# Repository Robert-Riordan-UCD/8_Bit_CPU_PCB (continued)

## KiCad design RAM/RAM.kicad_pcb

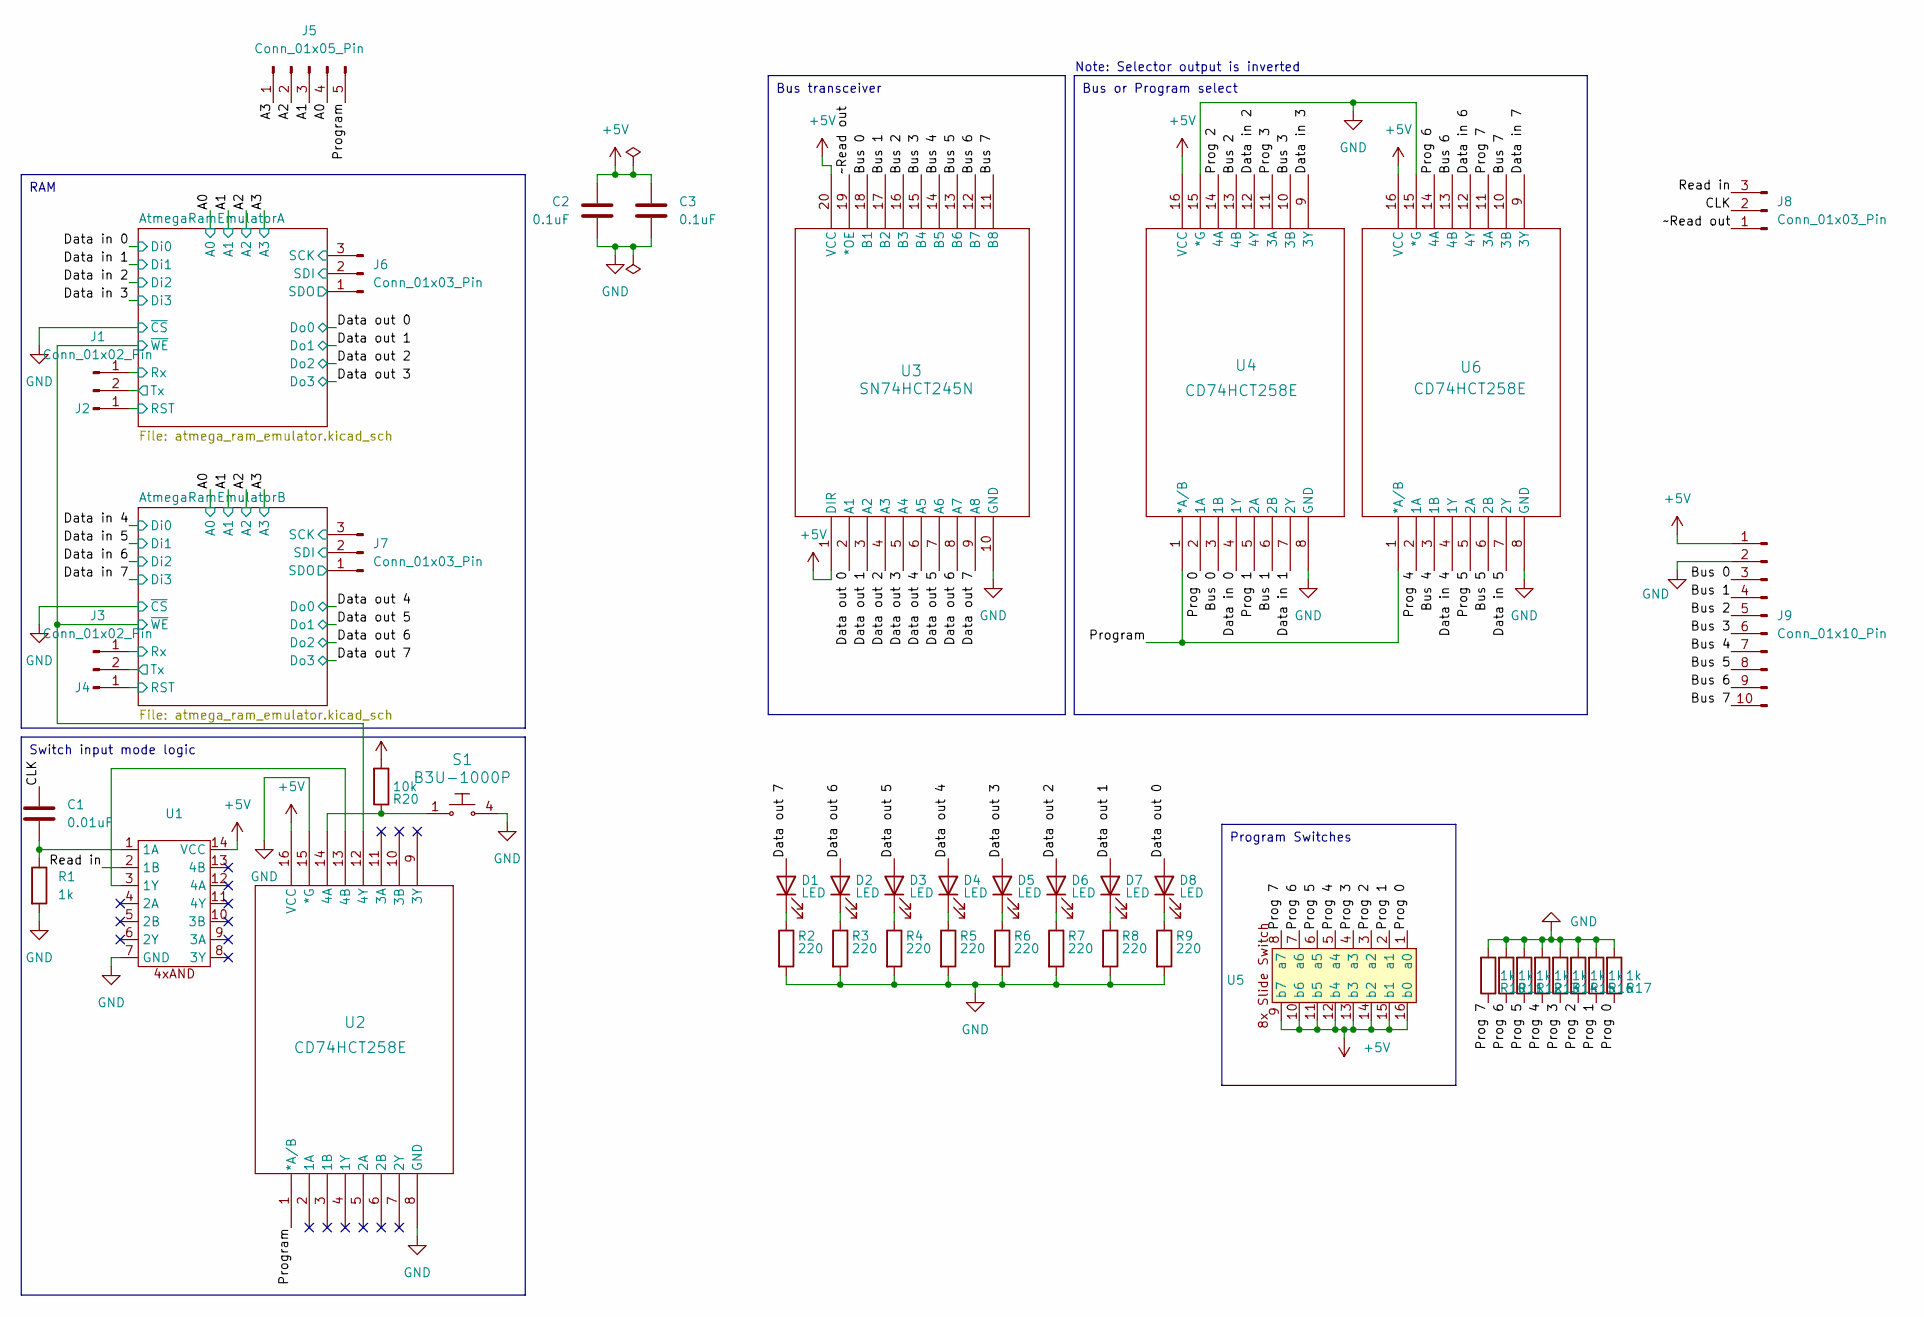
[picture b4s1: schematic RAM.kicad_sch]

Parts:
C1: 0.01uF; C_Disc_D5.0mm_W2.5mm_P2.50mm
C2, C3: 0.1uF; C_Disc_D5.0mm_W2.5mm_P2.50mm
D1, D2, D3, D4, D5, D6, D7, D8: LED; LED_D5.0mm
J1, J3: Conn_01x02_Pin; PinHeader_1x02_P2.54mm_Vertical
J2, J4: Conn_01x01_Pin; PinHeader_1x01_P2.54mm_Vertical
J5: Conn_01x05_Pin; PinHeader_1x05_P2.54mm_Vertical
J6, J7, J8: Conn_01x03_Pin; PinHeader_1x03_P2.54mm_Vertical
J9: Conn_01x10_Pin; PinHeader_1x10_P2.54mm_Vertical
R1, R10, R11, R12, R13, R14, R15, R16, R17: 1k; CF_series_Resistors_THT
R2, R3, R4, R5, R6, R7, R8, R9: 220; CF_series_Resistors_THT
R20: 10k; CF_series_Resistors_THT
S1: B3U-1000P; tactile_switch; MPN B3U-1000P; Digi-Key_PN SW1020CT-ND
U1: 4x_and
U2, U4, U6: CD74HCT258E; 2_to_1_selector
U3: SN74HCT245N; 8x_tristate_transceiver
U5: DIP-16_W7.62mm

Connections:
+5V: C2.1, C3.1, J9.1, R20.2, U1.14 (VCC), U2.16 (VCC), U3.1 (DIR), U3.20 (VCC), U4.16 (VCC), U5.9 (b7), U5.10 (b6), U5.11 (b5), U5.12 (b4), U5.13 (b3), U5.14 (b2), U5.15 (b1), U5.16 (b0), U6.16 (VCC); also elsewhere on the board
/A0: J5.4; also elsewhere on the board
/A1: J5.3; also elsewhere on the board
/A2: J5.2; also elsewhere on the board
/A3: J5.1; also elsewhere on the board
/AtmegaRamEmulatorA/RST: J2.1; also elsewhere on the board
/AtmegaRamEmulatorA/Rx: J1.1; also elsewhere on the board
/AtmegaRamEmulatorA/SCK: J6.3; also elsewhere on the board
/AtmegaRamEmulatorA/SDI: J6.2; also elsewhere on the board
/AtmegaRamEmulatorA/SDO: J6.1; also elsewhere on the board
/AtmegaRamEmulatorA/Tx: J1.2; also elsewhere on the board
/AtmegaRamEmulatorA/~WE: U2.12 (4Y); also elsewhere on the board
/AtmegaRamEmulatorB/RST: J4.1; also elsewhere on the board
/AtmegaRamEmulatorB/Rx: J3.1; also elsewhere on the board
/AtmegaRamEmulatorB/SCK: J7.3; also elsewhere on the board
/AtmegaRamEmulatorB/SDI: J7.2; also elsewhere on the board
/AtmegaRamEmulatorB/SDO: J7.1; also elsewhere on the board
/AtmegaRamEmulatorB/Tx: J3.2; also elsewhere on the board
/Bus 0: J9.3, U3.18 (B1), U4.3 (1B)
/Bus 1: J9.4, U3.17 (B2), U4.6 (2B)
/Bus 2: J9.5, U3.16 (B3), U4.13 (4B)
/Bus 3: J9.6, U3.15 (B4), U4.10 (3B)
/Bus 4: J9.7, U3.14 (B5), U6.3 (1B)
/Bus 5: J9.8, U3.13 (B6), U6.6 (2B)
/Bus 6: J9.9, U3.12 (B7), U6.13 (4B)
/Bus 7: J9.10, U3.11 (B8), U6.10 (3B)
/CLK: C1.1, J8.2
/Data in 0: U4.4 (1Y); also elsewhere on the board
/Data in 1: U4.7 (2Y); also elsewhere on the board
/Data in 2: U4.12 (4Y); also elsewhere on the board
/Data in 3: U4.9 (3Y); also elsewhere on the board
/Data in 4: U6.4 (1Y); also elsewhere on the board
/Data in 5: U6.7 (2Y); also elsewhere on the board
/Data in 6: U6.12 (4Y); also elsewhere on the board
/Data in 7: U6.9 (3Y); also elsewhere on the board
/Data out 0: D8.2 (A), U3.2 (A1); also elsewhere on the board
/Data out 1: D7.2 (A), U3.3 (A2); also elsewhere on the board
/Data out 2: D6.2 (A), U3.4 (A3); also elsewhere on the board
/Data out 3: D5.2 (A), U3.5 (A4); also elsewhere on the board
/Data out 4: D4.2 (A), U3.6 (A5); also elsewhere on the board
/Data out 5: D3.2 (A), U3.7 (A6); also elsewhere on the board
/Data out 6: D2.2 (A), U3.8 (A7); also elsewhere on the board
/Data out 7: D1.2 (A), U3.9 (A8); also elsewhere on the board
/Prog 0: R17.1, U4.2 (1A), U5.1 (a0)
/Prog 1: R16.1, U4.5 (2A), U5.2 (a1)
/Prog 2: R15.1, U4.14 (4A), U5.3 (a2)
/Prog 3: R14.1, U4.11 (3A), U5.4 (a3)
/Prog 4: R13.1, U5.5 (a4), U6.2 (1A)
/Prog 5: R12.1, U5.6 (a5), U6.5 (2A)
/Prog 6: R11.1, U5.7 (a6), U6.14 (4A)
/Prog 7: R10.1, U5.8 (a7), U6.11 (3A)
/Program: J5.5, U2.1 (*A/B), U4.1 (*A/B), U6.1 (*A/B)
/Read in: J8.3, U1.2 (1B)
/~Read out: J8.1, U3.19 (*OE)
GND: C2.2, C3.2, J9.2, R1.2, R2.2, R3.2, R4.2, R5.2, R6.2, R7.2, R8.2, R9.2, R10.2, R11.2, R12.2, R13.2, R14.2, R15.2, R16.2, R17.2, S1.4, U1.7 (GND), U2.8 (GND), U2.15 (*G), U3.10 (GND), U4.8 (GND), U4.15 (*G), U6.8 (GND), U6.15 (*G); also elsewhere on the board
unnamed: D1.1 (K), R2.1
unnamed: D2.1 (K), R3.1
unnamed: D3.1 (K), R4.1
unnamed: D4.1 (K), R5.1
unnamed: D5.1 (K), R6.1
unnamed: D6.1 (K), R7.1
unnamed: D7.1 (K), R8.1
unnamed: D8.1 (K), R9.1
unnamed: C1.2, R1.1, U1.1 (1A)
unnamed: U1.3 (1Y), U2.13 (4B)
unnamed: R20.1, S1.1, U2.14 (4A)

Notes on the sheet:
Program Switches
Switch input mode logic
Bus or Program select
RAM
Bus transceiver
Note: Selector output is inverted

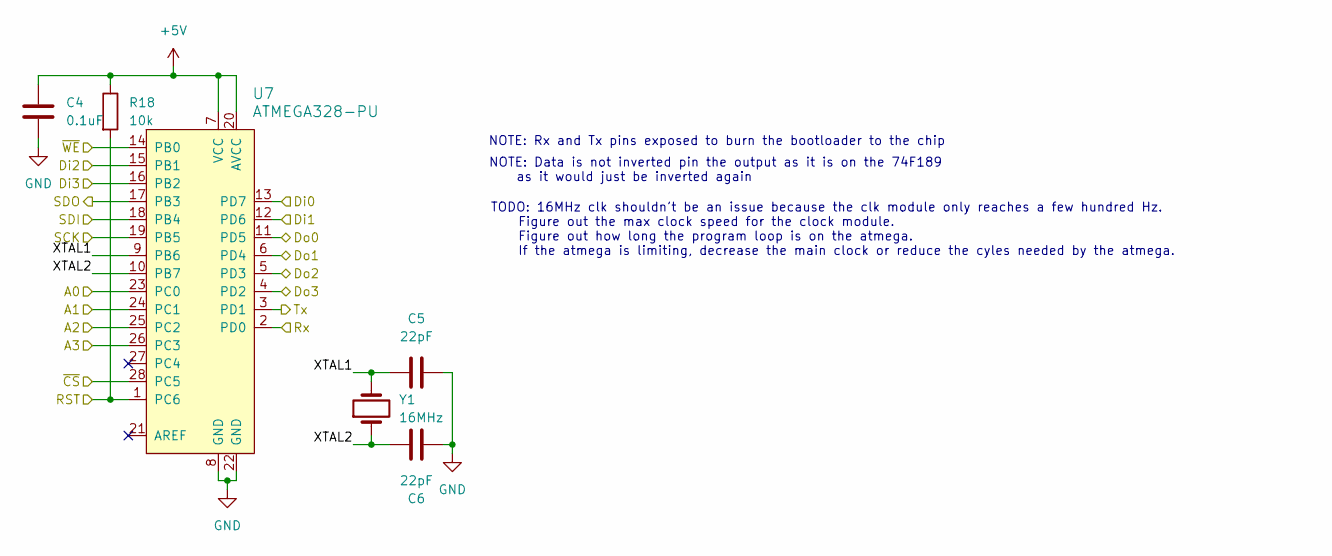
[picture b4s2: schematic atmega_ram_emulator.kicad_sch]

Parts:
C4: 0.1uF; Cp_2mm_pin_spacing
C5, C6: 22pF; C_Disc_D5.0mm_W2.5mm_P2.50mm
R18: 10k; CF_series_Resistors_THT
U7: ATMEGA328-PU; DIP787W46P254L3467H508Q28; MPN ATMEGA328-PU; Digi-Key_PN ATMEGA328-PU-ND
Y1: 16MHz; 16MHzCrystalOscillator

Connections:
+5V: C4.1, R18.1, U7.7 (VCC), U7.20 (AVCC); also elsewhere on the board
/A0: U7.23 (PC0); also elsewhere on the board
/A1: U7.24 (PC1); also elsewhere on the board
/A2: U7.25 (PC2); also elsewhere on the board
/A3: U7.26 (PC3); also elsewhere on the board
/AtmegaRamEmulatorA/RST: R18.2, U7.1 (PC6); also elsewhere on the board
/AtmegaRamEmulatorA/Rx: U7.2 (PD0); also elsewhere on the board
/AtmegaRamEmulatorA/SCK: U7.19 (PB5); also elsewhere on the board
/AtmegaRamEmulatorA/SDI: U7.18 (PB4); also elsewhere on the board
/AtmegaRamEmulatorA/SDO: U7.17 (PB3); also elsewhere on the board
/AtmegaRamEmulatorA/Tx: U7.3 (PD1); also elsewhere on the board
/AtmegaRamEmulatorA/XTAL1: C5.1, U7.9 (PB6), Y1.2
/AtmegaRamEmulatorA/XTAL2: C6.2, U7.10 (PB7), Y1.1
/AtmegaRamEmulatorA/~WE: U7.14 (PB0); also elsewhere on the board
/Data in 0: U7.13 (PD7); also elsewhere on the board
/Data in 1: U7.12 (PD6); also elsewhere on the board
/Data in 2: U7.15 (PB1); also elsewhere on the board
/Data in 3: U7.16 (PB2); also elsewhere on the board
/Data out 0: U7.11 (PD5); also elsewhere on the board
/Data out 1: U7.6 (PD4); also elsewhere on the board
/Data out 2: U7.5 (PD3); also elsewhere on the board
/Data out 3: U7.4 (PD2); also elsewhere on the board
GND: C4.2, C5.2, C6.1, U7.8 (GND), U7.22 (GND), U7.28 (PC5); also elsewhere on the board

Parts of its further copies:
C7: 0.1uF; Cp_2mm_pin_spacing
C8, C9: 22pF; C_Disc_D5.0mm_W2.5mm_P2.50mm
R19: 10k; CF_series_Resistors_THT
U8: ATMEGA328-PU; DIP787W46P254L3467H508Q28; MPN ATMEGA328-PU; Digi-Key_PN ATMEGA328-PU-ND
Y2: 16MHz; 16MHzCrystalOscillator

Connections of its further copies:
+5V: C7.1, R19.1, U8.7 (VCC), U8.20 (AVCC); also elsewhere on the board
/A0: U8.23 (PC0); also elsewhere on the board
/A1: U8.24 (PC1); also elsewhere on the board
/A2: U8.25 (PC2); also elsewhere on the board
/A3: U8.26 (PC3); also elsewhere on the board
/AtmegaRamEmulatorA/~WE: U8.14 (PB0); also elsewhere on the board
/AtmegaRamEmulatorB/RST: R19.2, U8.1 (PC6); also elsewhere on the board
/AtmegaRamEmulatorB/Rx: U8.2 (PD0); also elsewhere on the board
/AtmegaRamEmulatorB/SCK: U8.19 (PB5); also elsewhere on the board
/AtmegaRamEmulatorB/SDI: U8.18 (PB4); also elsewhere on the board
/AtmegaRamEmulatorB/SDO: U8.17 (PB3); also elsewhere on the board
/AtmegaRamEmulatorB/Tx: U8.3 (PD1); also elsewhere on the board
/AtmegaRamEmulatorB/XTAL1: C8.1, U8.9 (PB6), Y2.2
/AtmegaRamEmulatorB/XTAL2: C9.2, U8.10 (PB7), Y2.1
/Data in 4: U8.13 (PD7); also elsewhere on the board
/Data in 5: U8.12 (PD6); also elsewhere on the board
/Data in 6: U8.15 (PB1); also elsewhere on the board
/Data in 7: U8.16 (PB2); also elsewhere on the board
/Data out 4: U8.11 (PD5); also elsewhere on the board
/Data out 5: U8.6 (PD4); also elsewhere on the board
/Data out 6: U8.5 (PD3); also elsewhere on the board
/Data out 7: U8.4 (PD2); also elsewhere on the board
GND: C7.2, C8.2, C9.1, U8.8 (GND), U8.22 (GND), U8.28 (PC5); also elsewhere on the board

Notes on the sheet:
NOTE: Rx and Tx pins exposed to burn the bootloader to the chip
TODO: 16MHz clk shouldn't be an issue because the clk module only reaches a few hundred Hz. Figure out the max clock speed for the clock module. Figure out how long the program loop is on the atmega. If the atmega is limiting, decrease the main clock or reduce the cyles needed by the atmega.
NOTE: Data is not inverted pin the output as it is on the 74F189 as it would just be inverted again

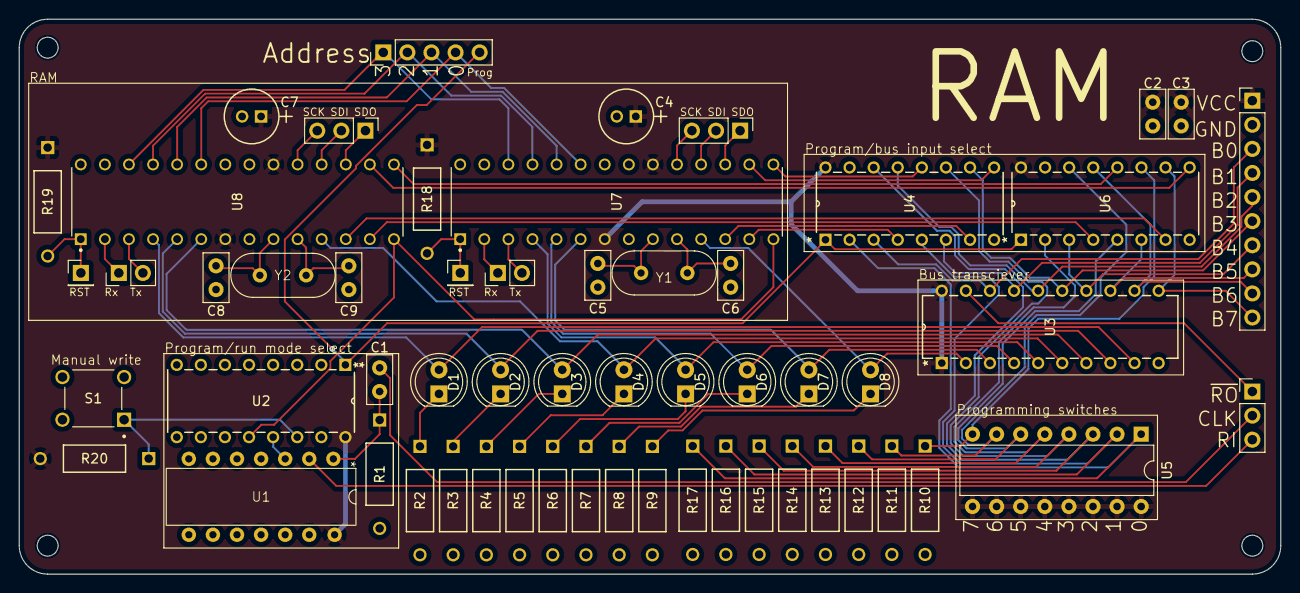
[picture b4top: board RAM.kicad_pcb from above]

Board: 2 copper layers, 133.0 x 58.5 mm, 57 parts (0 on the bottom side), 70 nets.

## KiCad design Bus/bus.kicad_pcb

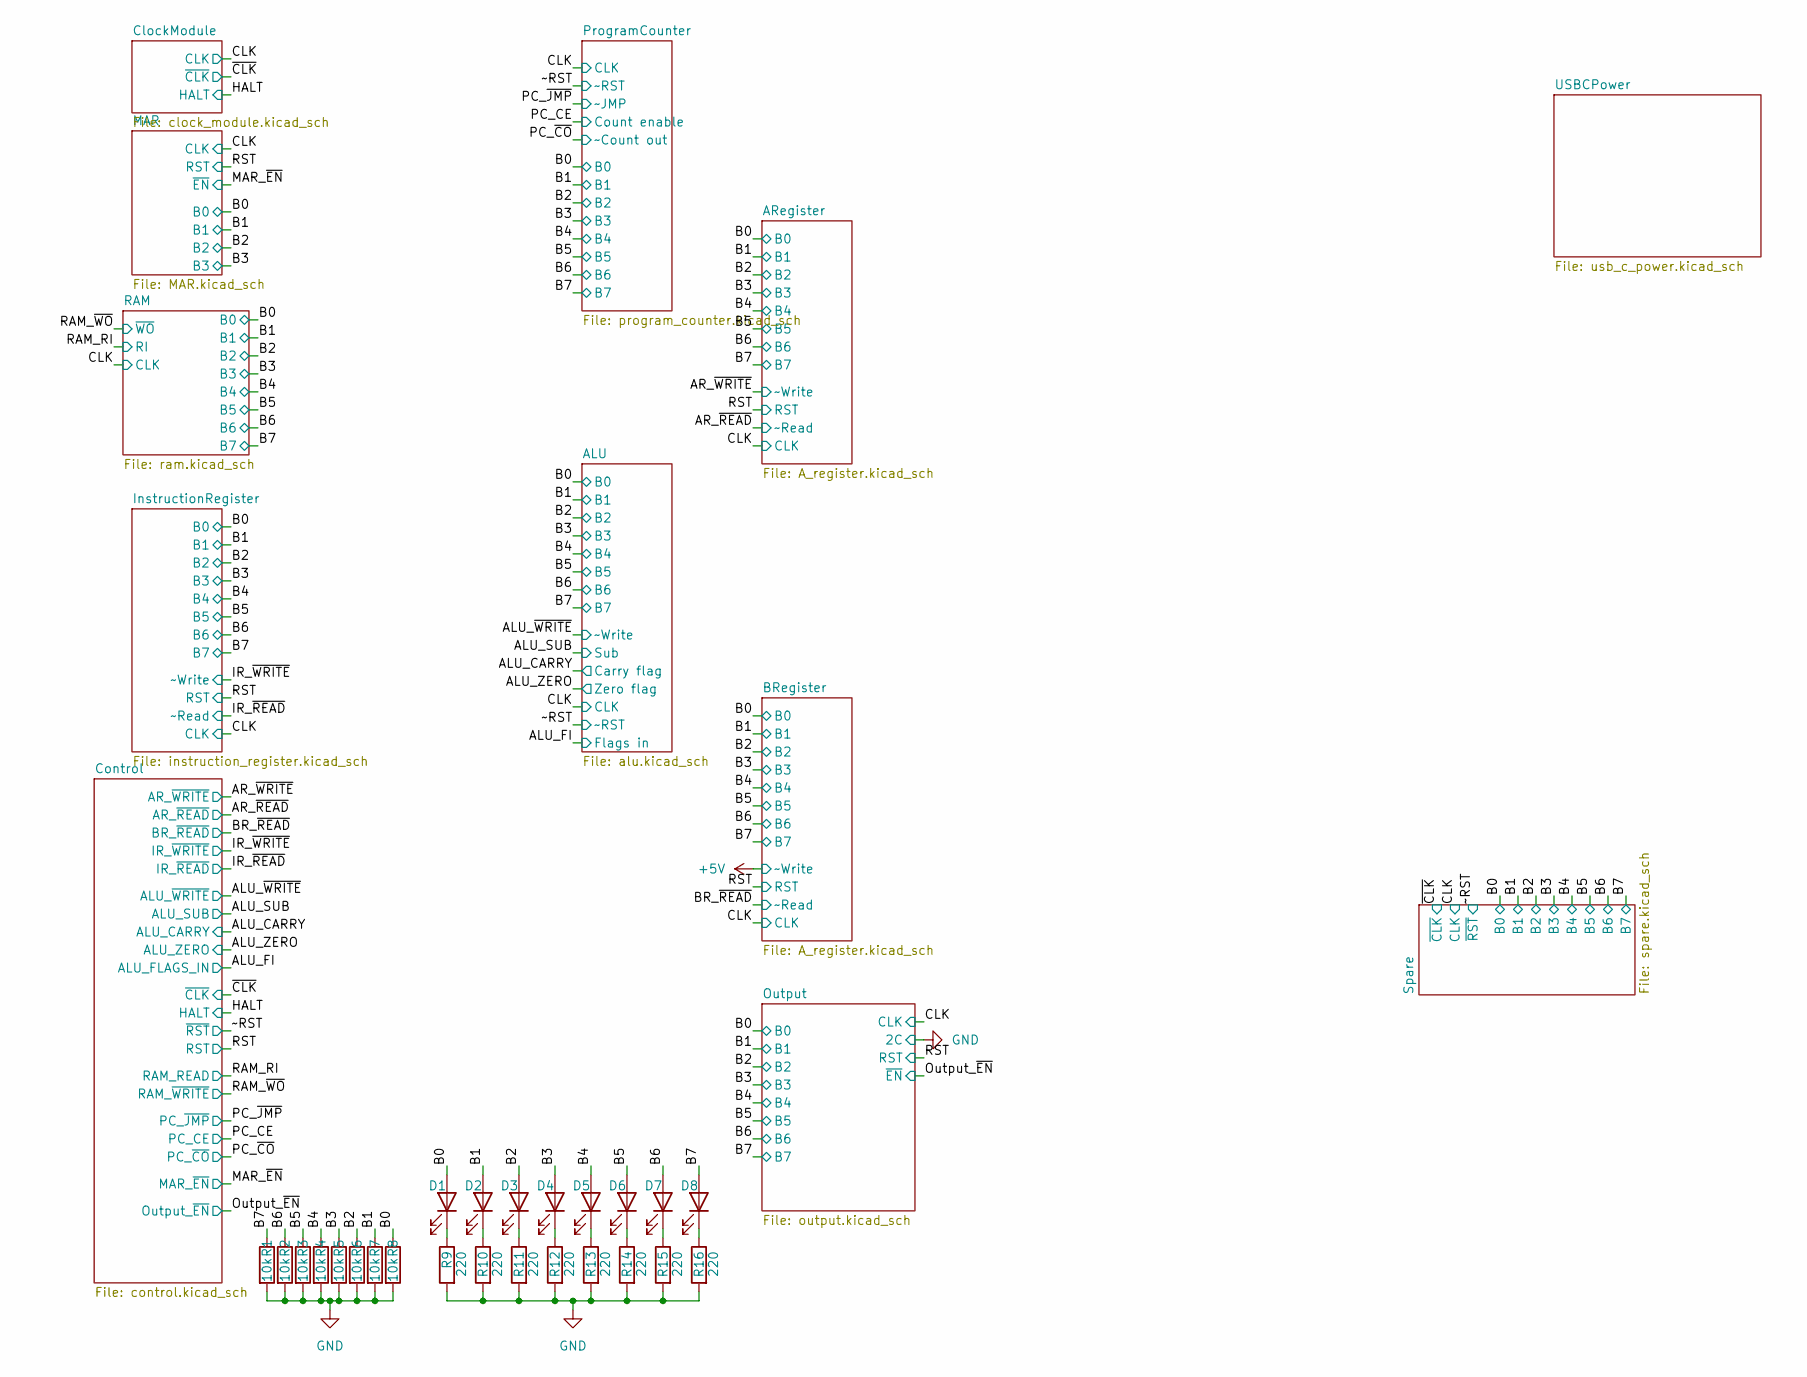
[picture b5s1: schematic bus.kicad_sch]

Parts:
D1, D2, D3, D4, D5, D6, D7, D8: LED; LED_D5.0mm
R1, R2, R3, R4, R5, R6, R7, R8: 10k; CF_series_Resistors_THT
R9, R10, R11, R12, R13, R14, R15, R16: 220; CF_series_Resistors_THT

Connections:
/B0: D1.2 (A), R8.1; also elsewhere on the board
/B1: D2.2 (A), R7.1; also elsewhere on the board
/B2: D3.2 (A), R6.1; also elsewhere on the board
/B3: D4.2 (A), R5.1; also elsewhere on the board
/B4: D5.2 (A), R4.1; also elsewhere on the board
/B5: D6.2 (A), R3.1; also elsewhere on the board
/B6: D7.2 (A), R2.1; also elsewhere on the board
/B7: D8.2 (A), R1.1; also elsewhere on the board
GND: R1.2, R2.2, R3.2, R4.2, R5.2, R6.2, R7.2, R8.2, R9.2, R10.2, R11.2, R12.2, R13.2, R14.2, R15.2, R16.2; also elsewhere on the board
unnamed: D1.1 (K), R9.1
unnamed: D2.1 (K), R10.1
unnamed: D3.1 (K), R11.1
unnamed: D4.1 (K), R12.1
unnamed: D5.1 (K), R13.1
unnamed: D6.1 (K), R14.1
unnamed: D7.1 (K), R15.1
unnamed: D8.1 (K), R16.1

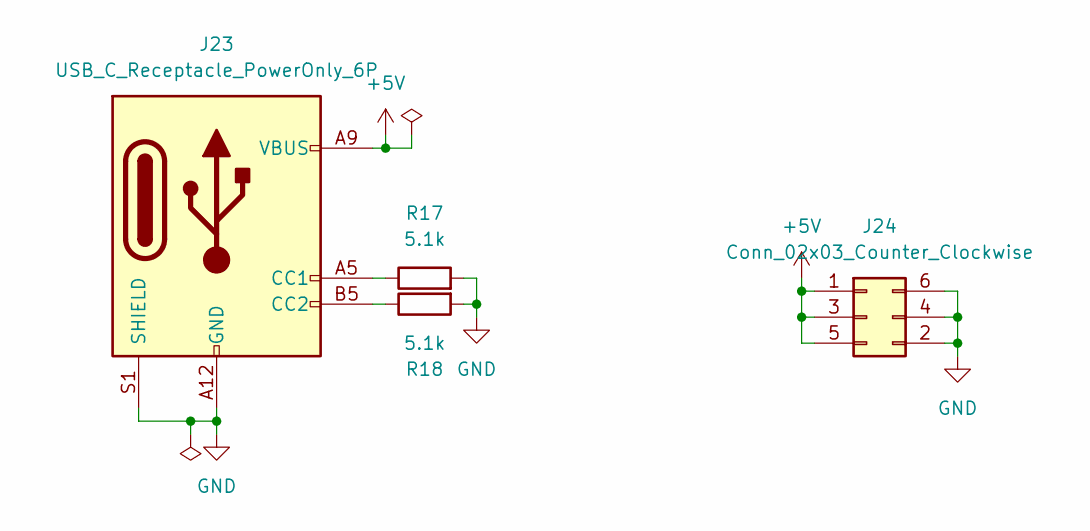
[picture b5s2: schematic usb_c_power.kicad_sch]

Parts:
J23: USB_C_Receptacle_PowerOnly_6P; USB_C_Receptacle_GCT_USB4085
J24: Conn_02x03_Counter_Clockwise; PinHeader_2x03_P2.54mm_Vertical
R17, R18: 5.1k; CF_series_Resistors_THT

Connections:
+5V: J23.A9 (VBUS), J23.B9 (VBUS), J24.1, J24.3 (Pin_2), J24.5 (Pin_3); also elsewhere on the board
GND: J23.A12 (GND), J23.B12 (GND), J23.S1 (SHIELD), J24.2 (Pin_4), J24.4 (Pin_5), J24.6, R17.2, R18.2; also elsewhere on the board
unnamed: J23.A5 (CC1), R17.1
unnamed: J23.B5 (CC2), R18.1

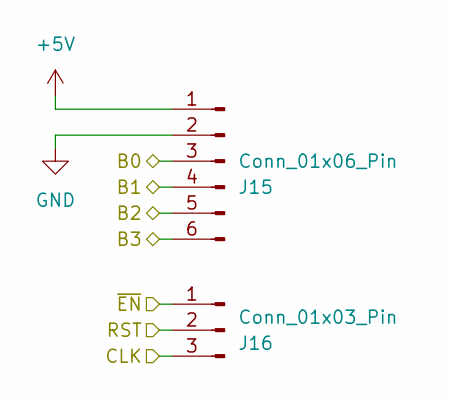
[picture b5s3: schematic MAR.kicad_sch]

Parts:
J15: Conn_01x06_Pin; PinHeader_1x06_P2.54mm_Vertical
J16: Conn_01x03_Pin; PinHeader_1x03_P2.54mm_Vertical

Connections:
+5V: J15.1; also elsewhere on the board
/B0: J15.3; also elsewhere on the board
/B1: J15.4; also elsewhere on the board
/B2: J15.5; also elsewhere on the board
/B3: J15.6; also elsewhere on the board
/CLK: J16.3; also elsewhere on the board
/MAR_~EN: J16.1; also elsewhere on the board
/RST: J16.2; also elsewhere on the board
GND: J15.2; also elsewhere on the board

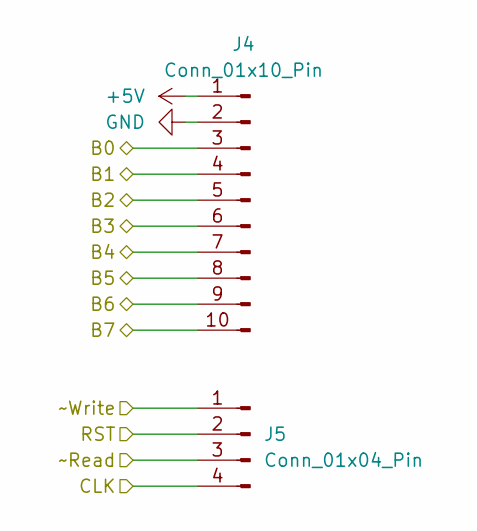
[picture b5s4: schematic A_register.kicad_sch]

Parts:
J4: Conn_01x10_Pin; PinHeader_1x10_P2.54mm_Vertical
J5: Conn_01x04_Pin; PinHeader_1x04_P2.54mm_Vertical

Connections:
+5V: J4.1, J5.1; also elsewhere on the board
/B0: J4.3; also elsewhere on the board
/B1: J4.4; also elsewhere on the board
/B2: J4.5; also elsewhere on the board
/B3: J4.6; also elsewhere on the board
/B4: J4.7; also elsewhere on the board
/B5: J4.8; also elsewhere on the board
/B6: J4.9; also elsewhere on the board
/B7: J4.10; also elsewhere on the board
/BR_~READ: J5.3; also elsewhere on the board
/CLK: J5.4; also elsewhere on the board
/RST: J5.2; also elsewhere on the board
GND: J4.2; also elsewhere on the board

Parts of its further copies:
J2: Conn_01x10_Pin; PinHeader_1x10_P2.54mm_Vertical
J3: Conn_01x04_Pin; PinHeader_1x04_P2.54mm_Vertical

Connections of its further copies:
+5V: J2.1; also elsewhere on the board
/AR_~READ: J3.3; also elsewhere on the board
/AR_~WRITE: J3.1; also elsewhere on the board
/B0: J2.3; also elsewhere on the board
/B1: J2.4; also elsewhere on the board
/B2: J2.5; also elsewhere on the board
/B3: J2.6; also elsewhere on the board
/B4: J2.7; also elsewhere on the board
/B5: J2.8; also elsewhere on the board
/B6: J2.9; also elsewhere on the board
/B7: J2.10; also elsewhere on the board
/CLK: J3.4; also elsewhere on the board
/RST: J3.2; also elsewhere on the board
GND: J2.2; also elsewhere on the board

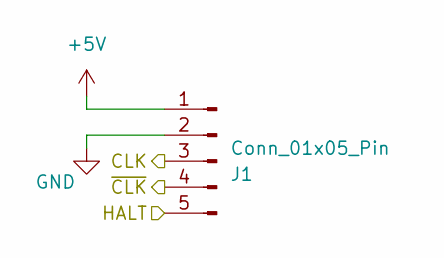
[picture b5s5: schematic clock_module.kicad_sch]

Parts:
J1: Conn_01x05_Pin; PinHeader_1x05_P2.54mm_Vertical

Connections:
+5V: J1.1; also elsewhere on the board
/CLK: J1.3; also elsewhere on the board
/HALT: J1.5; also elsewhere on the board
/~CLK: J1.4; also elsewhere on the board
GND: J1.2; also elsewhere on the board

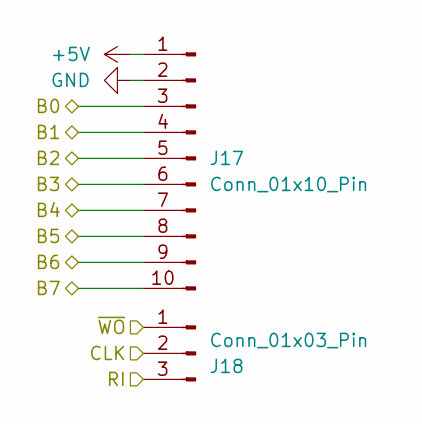
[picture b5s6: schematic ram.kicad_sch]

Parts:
J17: Conn_01x10_Pin; PinHeader_1x10_P2.54mm_Vertical
J18: Conn_01x03_Pin; PinHeader_1x03_P2.54mm_Vertical

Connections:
+5V: J17.1; also elsewhere on the board
/B0: J17.3; also elsewhere on the board
/B1: J17.4; also elsewhere on the board
/B2: J17.5; also elsewhere on the board
/B3: J17.6; also elsewhere on the board
/B4: J17.7; also elsewhere on the board
/B5: J17.8; also elsewhere on the board
/B6: J17.9; also elsewhere on the board
/B7: J17.10; also elsewhere on the board
/CLK: J18.2; also elsewhere on the board
/RAM_RI: J18.3; also elsewhere on the board
/RAM_~WO: J18.1; also elsewhere on the board
GND: J17.2; also elsewhere on the board

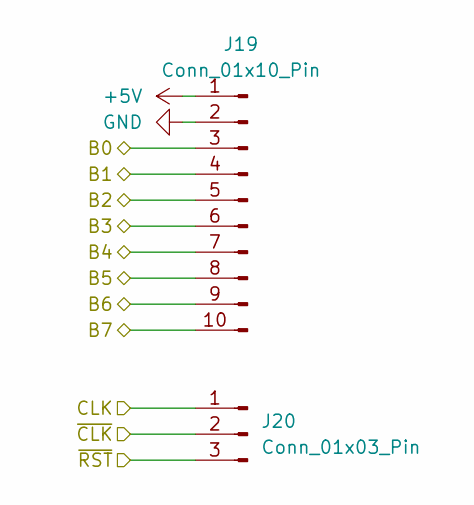
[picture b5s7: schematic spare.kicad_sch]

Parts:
J19: Conn_01x10_Pin; PinHeader_1x10_P2.54mm_Vertical
J20: Conn_01x03_Pin; PinHeader_1x03_P2.54mm_Vertical

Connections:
+5V: J19.1; also elsewhere on the board
/B0: J19.3; also elsewhere on the board
/B1: J19.4; also elsewhere on the board
/B2: J19.5; also elsewhere on the board
/B3: J19.6; also elsewhere on the board
/B4: J19.7; also elsewhere on the board
/B5: J19.8; also elsewhere on the board
/B6: J19.9; also elsewhere on the board
/B7: J19.10; also elsewhere on the board
/CLK: J20.1; also elsewhere on the board
/~RST: J20.3; also elsewhere on the board
/~CLK: J20.2; also elsewhere on the board
GND: J19.2; also elsewhere on the board

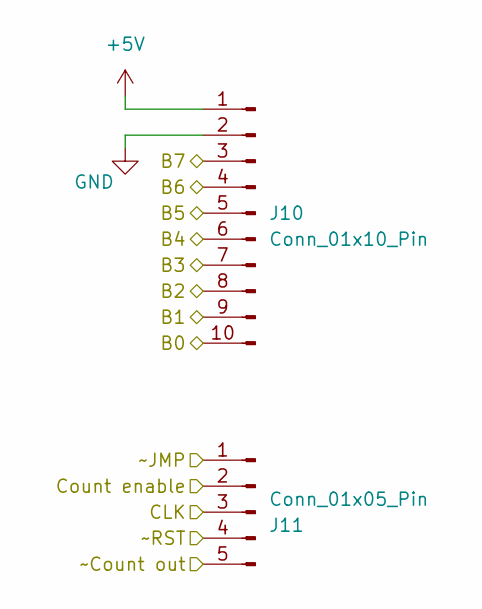
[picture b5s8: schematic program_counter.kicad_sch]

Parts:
J10: Conn_01x10_Pin; PinHeader_1x10_P2.54mm_Vertical
J11: Conn_01x05_Pin; PinHeader_1x05_P2.54mm_Vertical

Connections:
+5V: J10.1; also elsewhere on the board
/B0: J10.10; also elsewhere on the board
/B1: J10.9; also elsewhere on the board
/B2: J10.8; also elsewhere on the board
/B3: J10.7; also elsewhere on the board
/B4: J10.6; also elsewhere on the board
/B5: J10.5; also elsewhere on the board
/B6: J10.4; also elsewhere on the board
/B7: J10.3; also elsewhere on the board
/CLK: J11.3; also elsewhere on the board
/PC_CE: J11.2; also elsewhere on the board
/PC_~CO: J11.5; also elsewhere on the board
/PC_~JMP: J11.1; also elsewhere on the board
/~RST: J11.4; also elsewhere on the board
GND: J10.2; also elsewhere on the board

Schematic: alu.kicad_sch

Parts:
J8: Conn_01x10_Pin; PinHeader_1x10_P2.54mm_Vertical
J9: Conn_01x07_Pin; PinHeader_1x07_P2.54mm_Vertical

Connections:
+5V: J8.1; also elsewhere on the board
/ALU_CARRY: J9.6; also elsewhere on the board
/ALU_FI: J9.5; also elsewhere on the board
/ALU_SUB: J9.2; also elsewhere on the board
/ALU_ZERO: J9.7; also elsewhere on the board
/ALU_~WRITE: J9.1; also elsewhere on the board
/B0: J8.10; also elsewhere on the board
/B1: J8.9; also elsewhere on the board
/B2: J8.8; also elsewhere on the board
/B3: J8.7; also elsewhere on the board
/B4: J8.6; also elsewhere on the board
/B5: J8.5; also elsewhere on the board
/B6: J8.4; also elsewhere on the board
/B7: J8.3; also elsewhere on the board
/CLK: J9.4; also elsewhere on the board
/~RST: J9.3; also elsewhere on the board
GND: J8.2; also elsewhere on the board

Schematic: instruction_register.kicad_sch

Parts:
J6: Conn_01x10_Pin; PinHeader_1x10_P2.54mm_Vertical
J7: Conn_01x04_Pin; PinHeader_1x04_P2.54mm_Vertical

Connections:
+5V: J6.1; also elsewhere on the board
/B0: J6.3; also elsewhere on the board
/B1: J6.4; also elsewhere on the board
/B2: J6.5; also elsewhere on the board
/B3: J6.6; also elsewhere on the board
/B4: J6.7; also elsewhere on the board
/B5: J6.8; also elsewhere on the board
/B6: J6.9; also elsewhere on the board
/B7: J6.10; also elsewhere on the board
/CLK: J7.1; also elsewhere on the board
/IR_~READ: J7.2; also elsewhere on the board
/IR_~WRITE: J7.4; also elsewhere on the board
/RST: J7.3; also elsewhere on the board
GND: J6.2; also elsewhere on the board

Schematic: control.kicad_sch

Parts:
J12: Conn_01x07_Pin; PinHeader_1x07_P2.54mm_Vertical
J13, J14: Conn_01x08_Pin; PinHeader_1x08_P2.54mm_Vertical

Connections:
+5V: J12.1; also elsewhere on the board
/ALU_CARRY: J12.3; also elsewhere on the board
/ALU_FI: J14.6; also elsewhere on the board
/ALU_SUB: J14.5; also elsewhere on the board
/ALU_ZERO: J12.4; also elsewhere on the board
/ALU_~WRITE: J14.4; also elsewhere on the board
/AR_~READ: J14.3; also elsewhere on the board
/AR_~WRITE: J14.2; also elsewhere on the board
/BR_~READ: J14.7; also elsewhere on the board
/HALT: J13.6; also elsewhere on the board
/IR_~READ: J13.2; also elsewhere on the board
/IR_~WRITE: J13.1; also elsewhere on the board
/MAR_~EN: J13.5; also elsewhere on the board
/Output_~EN: J14.8; also elsewhere on the board
/PC_CE: J13.8; also elsewhere on the board
/PC_~CO: J14.1; also elsewhere on the board
/PC_~JMP: J13.7; also elsewhere on the board
/RAM_RI: J13.3; also elsewhere on the board
/RAM_~WO: J13.4; also elsewhere on the board
/RST: J12.7; also elsewhere on the board
/~RST: J12.6; also elsewhere on the board
/~CLK: J12.5; also elsewhere on the board
GND: J12.2; also elsewhere on the board

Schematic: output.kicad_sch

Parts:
J21: Conn_01x10_Pin; PinHeader_1x10_P2.54mm_Vertical
J22: Conn_01x04_Pin; PinHeader_1x04_P2.54mm_Vertical

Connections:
+5V: J21.1; also elsewhere on the board
/B0: J21.3; also elsewhere on the board
/B1: J21.4; also elsewhere on the board
/B2: J21.5; also elsewhere on the board
/B3: J21.6; also elsewhere on the board
/B4: J21.7; also elsewhere on the board
/B5: J21.8; also elsewhere on the board
/B6: J21.9; also elsewhere on the board
/B7: J21.10; also elsewhere on the board
/CLK: J22.4; also elsewhere on the board
/Output_~EN: J22.3; also elsewhere on the board
/RST: J22.2; also elsewhere on the board
GND: J21.2, J22.1; also elsewhere on the board

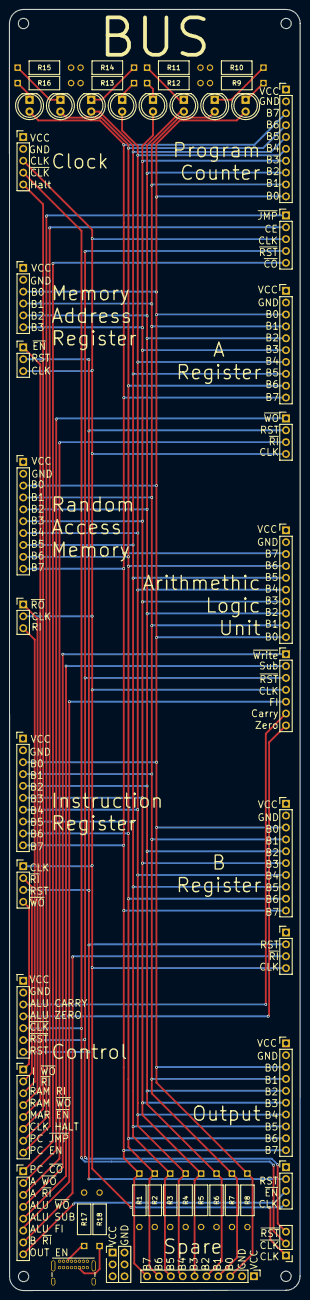
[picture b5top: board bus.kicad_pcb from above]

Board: 4 copper layers, 62.2 x 274.1 mm, 50 parts (0 on the bottom side), 42 nets.

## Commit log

2024-07-22 Added footprints and schematics that I have downloaded or created so far
2024-07-22 Clock module created and layedout on PCB
2024-07-22 Symbol library I've created so far
2024-07-22 Initial work on registers. Should be usable for both A and B, but unsure about instruction register. May need pins to come out the other side and only need 4 of the bits
2024-07-22 Initial work on bus. Clock, power, and bus pins from clock and registers connected in schematic
2024-07-22 ALU schematic setup without zero or carry output flags
2024-07-22 Assigned footprints
2024-07-22 ALU routed on PCB
2024-07-22 Added the ALU to the bus schematic
2024-07-22 Switched LEDs to MSB first. Added label to board.
2024-07-23 Created a script to emulate the 4-bit RAM chips on an arduino
2024-07-25 Added atmega schematic for RAM emulation
2024-07-25 RAM input selection schematic complete
2024-07-25 RAM output connected to bus
2024-07-25 Added logic to select between program or run mode signals
2024-07-25 RAM schematic complete
2024-07-25 Assigned footprints to all RAM components except crystal. No datasheet so waiting for delivery to hopefully get more detail or measure
2024-07-26 RAM module layout complete except footprint for crystal
2024-07-26 Memory address register schematic and PCB complete
2024-07-26 Exposed SPI and RST on atmega chips
2024-07-27 Updated RAM with accurate crystal footprints
2024-07-27 Program counter schematic and PCB laid out
2024-07-29 Final clock updates
2024-07-29 Fixed LED and pin footprints for MAR and cleaned up the layout
2024-07-29 Fixed LED and pin footprints for MAR and cleaned up the layout
    Fixed LED and pin footprints for MAR and cleaned up the layout
2024-08-03 Inital output design. Need to test to validate design works
2024-08-03 Addded ALU flags register and laided out the PCB again
2024-08-04 4x NOR pinout was wrong. Updated with correct pinout. Fixed 2x D flip-flop references
2024-08-10 Fixed NOR schematic labeled as OR in ALU
2024-08-10 ALU layout complete
    ALU layout complete
2024-08-12 Fixed push button always shorting
2024-08-12 Fixed double throw switch footprint
2024-08-15 Some initial bus layout
2024-08-19 Switch pull up resistor was connected to wrong pin. Connected to switch now
2024-08-21 Created some simple tests to validate the PC
2024-08-29 Finished routing for registers. Silkscreen and PCB shape needs to be finalized.
2024-08-30 Register layout complete.
2024-08-30 Fixed misrouted bus connections to MUX. MUX is inverting so adde inverterto invert back. Slide switch should be conencted to power and pulled to ground. Breadboard validated.
2024-08-31 MAR layout complete
2024-08-31 Added Build output folder
2024-08-31 Minor silkscreen fixes
2024-09-01 Added more wiggle room to the double throw switch footprint. PCBs ordered for MAR/ALU/Registers
2024-09-06 Updated RAM arduino script to match pins to PCB
2024-09-06 Updated bus schematics with pinout of MAR/ALU/Registers on PCBs ordered
2024-09-12 Fixed registers silkscreen errors
2024-09-12 Added a test script to validate the A register
2024-09-14 Removed serial communication from RAM emulator. ATMega328-PU chips are now finally fully working as RAM chips. Get ATMega328P chips for any future projects.
2024-09-16 MAR Bus silkscreen was backwards
2024-09-16 Manufacturer footprint and data sheet seem to be wrong for the mux. Input for bits 3 and 4 are swapped.
2024-09-18 Updated RAM push button to use pins that aren't shorted together
2024-09-18 Ignore Build directory
2024-09-18 Updated RAM pin headers to 2.54mm and correct assignment
2024-09-18 Updated RAM LED footprints
2024-09-18 Removed pluggin generated files
2024-09-18 Reduced RAM layout
2024-09-19 RAM cosmetic updates
2024-09-19 Added pullup resistors to the programming switches
2024-09-19 Reconnected ~RO. Cosmetic updates
2024-09-20 Fixed incorrect MUX inputs on RAM
2024-09-20 Simulation of the clock edge detector to verify it works because the LEDs/arduino/my eyes aren't fast enough
2024-09-23 Swapped Run and Prog silk screen to match reality
2024-09-25 Forgot Flags register input enable. Passing clock though spare AND gate with new input Flag In input to create equvilant
2024-10-02 Initial EEPROM programmer. Can read and write, but I haven't added any useful data yet
2024-10-02 Initial Control schematic designed
2024-10-02 Control routed on PCB
2024-10-02 Added silkscreen labels to control LEDs. And other minor silkscreen updates
2024-10-02 Added edge cuts and mounting holes to control PCB
2024-10-02 Added silkscrfeen labels to PCB IO pins
2024-10-03 Updated microcode timer LEDs to 1 hot signal instead of binary counter
2024-10-04 Moved tests to single validation directory
    Moved tests to single validation directory
2024-10-04 PC passing all tests
2024-10-04 Registers appear to be working correctly until internal state pins are connected to arduino. Without connections all tests are passing using the LEDs visually, but connecting seems to interfere with 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
2024-10-04 Added eeprom symbol and footprint to git
2024-10-04 Create License
2024-10-04 Added License to read me
2024-10-04 MAR validated in run mode. Need to replace broken slide switches for program mode.
2024-10-05 Added spare pins to control
2024-10-07 Updated bus schematic control pins and added spare bus connection
2024-10-07 Added RAM to bus
2024-10-07 Updated output to use 2 4-bit registers instead of 1 8-bit because that's what I have. No longer need the AND for clk enable as registers have an enable pin. Enable is now active low. Reset is now ac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
2024-10-07 Updated output to use eeprom and timing circuit instead of atmega a shift registers
2024-10-07 EEPROM programmer updated to write data for 7 segment display
2024-10-07 Output PCB routed
2024-10-07 Fixed digit order and segments for some digits
2024-10-07 Added silkscreen to IO and added edge cuts and mounting points
2024-10-07 Minor updates to layout and silk screen
2024-10-07 Shrank board size
2024-10-08 Removed old implemention schematics
2024-10-08 Made atmega RAM emulators invert the data, because the selector is inverting it on the way in. Also fixed bug using WE pin inverted.
2024-10-09 Final silkscreen updates
2024-10-09 Realigned silk screen on output control pins
2024-10-09 Updated bus schmatic pins to match final layouts
2024-10-09 Output enable should be active low so I updated control to pass it through an inverter
2024-10-09 Added ~clk to the spare signals
2024-10-09 Fixed mismatched RAM labels
2024-10-09 Added pins to bus PCB. Oh boy it's going to be long
2024-10-09 Added an extra power option if I can't solder the USB header
2024-10-10 Aligned bus pins with where they will fit when connected to the other modules
2024-10-10 Bus fully routed. Minor edits to control to match bus
2024-10-10 Bus silkscreen added to all pins
2024-10-10 Final bus silkscreen updates
2024-10-10 Bus/Control/Output/RAM PCBs finalized and ordered
2024-10-11 Initial idea for a bootloader.
2024-10-15 EEPROM programmer setup for programming according to my PCB layout
2024-10-16 Registers fully validated
2024-10-16 ALU validation test plan and setup
2024-10-16 A and B pass through tests passing
2024-10-16 2's complement pass through test working
2024-10-16 Bus floating test passing
2024-10-16 Added test added and passing
2024-10-16 Subtract test added and passing
2024-10-16 Flags tests added and passing
2024-10-16 Flag reset tests added and passing. All ALU tests passing
2024-10-19 Minor silkscreen updates
2024-10-19 Connected unused control pins (B out/Output 2's Complement) to disabled values instead of floating
2024-10-20 Ouput bus was labeled incorectly. Labels fixed on output. Labels and connections fixed on bus
2024-10-21 Demux enable is active low. Should have been connected to ground not power
2024-10-23 Added a pull up resistor to the programming button
2024-10-23 Fixed barely connected power wire
2024-10-23 Removed redundent code
2024-10-23 Atmega uses interrupts instead of polling to monitor for write signal to prevent missing the signal
2024-10-28 Ignore step files
2024-10-28 Used Ben Eaters programmer with slight modifications to get the control EEPROMs working. My EEPROMs seem to be very touchy and I can't figure out why
2024-10-30 Modified version of Ben Eaters programmer used to get my output working
2024-10-31 RAM validation setup
2024-10-31 Write/read to all addresses passing
2024-10-31 RAM noop test passing
2024-10-31 RAM write/read to all values test written. Currently failing random tests. I think there are 2 issues; 1 - connectivity of the atmegas in the header pins doesn't seem to be 100% all the time, 2 - the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
2024-10-31 RAM program mode test added and passing
2024-10-31 Output validation setup
2024-10-31 Output count all test passing
2024-10-31 Output enable test passing
2024-10-31 Output reset test passing
2024-10-31 Output twos complement test added. -128/-126/-117 are not displaying for me but I think this is because these addresses are dead on my eeproms
2024-10-31 Control validation set up
2024-10-31 Control tests for all non-conditional instructions. Currently failing randomly-ish. I think the signal integreity from the instruction register is not great into the EEPROM headers
2024-11-01 Conditional jump tests added and passing
2024-11-01 Atmega ram emulators now boot with a program to count in 3s preloaded
2024-11-01 Control reset signals were inverted
2024-11-01 Added pulling resistors to unused pins from bus. (Output 2s comp & B reg write out)
2024-11-14 Updated ram programmer to make it easier preload programs
2024-11-27 Created a laser cut template to test a mounting design
2025-01-15 Added link to a video of the computer running
